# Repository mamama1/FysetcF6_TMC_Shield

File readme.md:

This shield has been inspired from the great SilentStepStick Protector boards by Watterott.
Source, see https://github.com/watterott/SilentStepStick

Some silkscreen has been stripped but besides that, Watterott's design has been used completely unchanged regarding the protection diode circuitry.

This board allows you to apply up to 42V (max. recommended) or up to 50V (absolute maximum, not recommended) to your motors by not connecting the VM pin to the F6 mainboard.

This repository has been released under the Creative Commons Attribution Share-Alike License: https://creativecommons.org/licenses/by-sa/4.0/

The original repository owned by Watterott, containing the SilentStepStick and Protector source files was released under the same license, see here: https://github.com/watterott/SilentStepStick/blob/master/README.md

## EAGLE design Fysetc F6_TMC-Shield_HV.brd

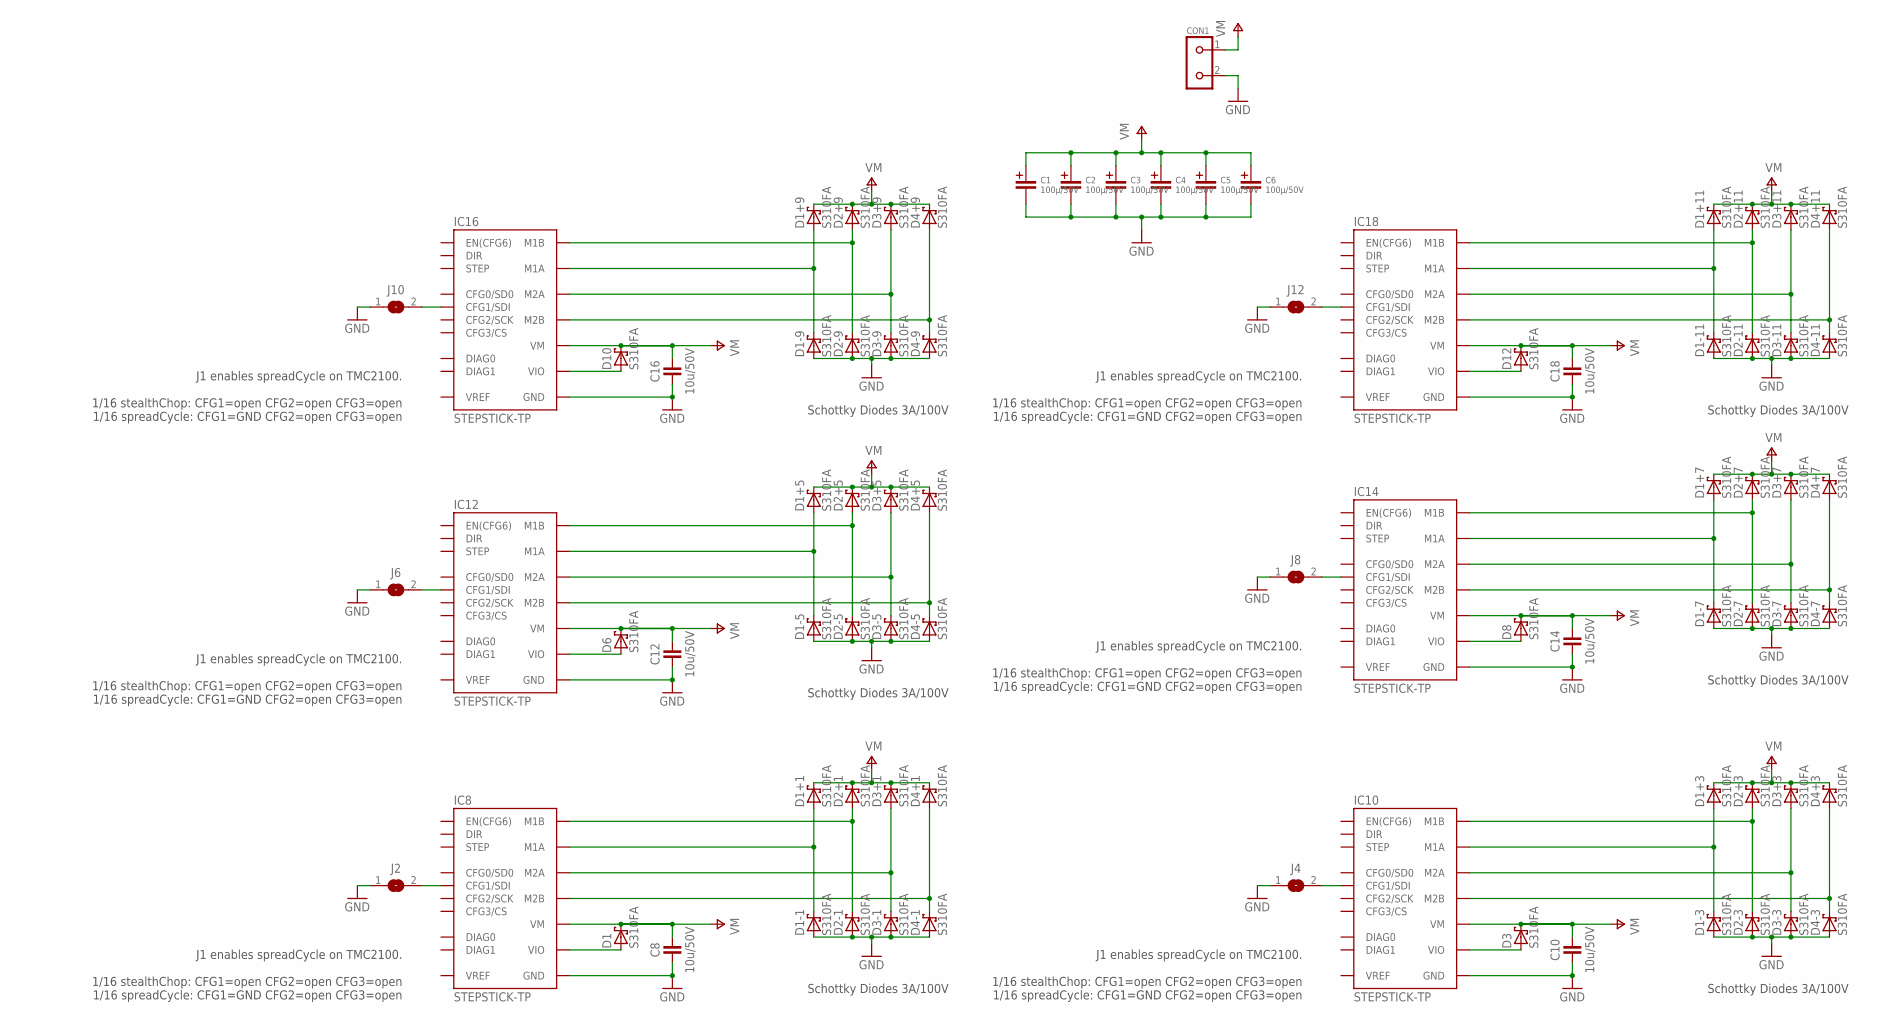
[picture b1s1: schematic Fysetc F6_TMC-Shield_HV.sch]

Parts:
C1, C2, C3, C4, C5, C6: 100µ/50V; C+/3.5/8
C8, C10, C12, C14, C16, C18: 10u/50V; C1210
CON1: KL2691311500002; KL2-691311500002
D1, D1+1, D1+3, D1+5, D1+7, D1+9, D1+11, D1-1, D1-3, D1-5, D1-7, D1-9, D1-11, D2+1, D2+3, D2+5, D2+7, D2+9, D2+11, D2-1, D2-3, D2-5, D2-7, D2-9, D2-11, D3, D3+1, D3+3, D3+5, D3+7, D3+9, D3+11, D3-1, D3-3, D3-5, D3-7, D3-9, D3-11, D4+1, D4+3, D4+5, D4+7, D4+9, D4+11, D4-1, D4-3, D4-5, D4-7, D4-9, D4-11, D6, D8, D10, D12: S310FA; SOD123
IC8, IC10, IC12, IC14, IC16, IC18: STEPSTICK-TP; STEPSTICK_TP
J2, J4, J6, J8, J10, J12: JUMPER2-0603-NC; JUMPER2-0603_NC

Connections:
GND: C1.-, C2.-, C3.-, C4.-, C5.-, C6.-, C8.1, C10.1, C12.1, C14.1, C16.1, C18.1, CON1.2, D1-1.A, D1-3.A, D1-5.A, D1-7.A, D1-9.A, D1-11.A, D2-1.A, D2-3.A, D2-5.A, D2-7.A, D2-9.A, D2-11.A, D3-1.A, D3-3.A, D3-5.A, D3-7.A, D3-9.A, D3-11.A, D4-1.A, D4-3.A, D4-5.A, D4-7.A, D4-9.A, D4-11.A, IC8.GND@1 (GND), IC8.GND@2 (GND), IC10.GND@1 (GND), IC10.GND@2 (GND), IC12.GND@1 (GND), IC12.GND@2 (GND), IC14.GND@1 (GND), IC14.GND@2 (GND), IC16.GND@1 (GND), IC16.GND@2 (GND), IC18.GND@1 (GND), IC18.GND@2 (GND), J2.1, J4.1, J6.1, J8.1, J10.1, J12.1
M1A1: D1+1.A, D1-1.C, IC8.M1A
M1A3: D1+3.A, D1-3.C, IC10.M1A
M1A5: D1+5.A, D1-5.C, IC12.M1A
M1A7: D1+7.A, D1-7.C, IC14.M1A
M1A9: D1+9.A, D1-9.C, IC16.M1A
M1A11: D1+11.A, D1-11.C, IC18.M1A
M1B1: D2+1.A, D2-1.C, IC8.M1B
M1B3: D2+3.A, D2-3.C, IC10.M1B
M1B5: D2+5.A, D2-5.C, IC12.M1B
M1B7: D2+7.A, D2-7.C, IC14.M1B
M1B9: D2+9.A, D2-9.C, IC16.M1B
M1B11: D2+11.A, D2-11.C, IC18.M1B
M2A1: D3+1.A, D3-1.C, IC8.M2A
M2A3: D3+3.A, D3-3.C, IC10.M2A
M2A5: D3+5.A, D3-5.C, IC12.M2A
M2A7: D3+7.A, D3-7.C, IC14.M2A
M2A9: D3+9.A, D3-9.C, IC16.M2A
M2A11: D3+11.A, D3-11.C, IC18.M2A
M2B1: D4+1.A, D4-1.C, IC8.M2B
M2B3: D4+3.A, D4-3.C, IC10.M2B
M2B5: D4+5.A, D4-5.C, IC12.M2B
M2B7: D4+7.A, D4-7.C, IC14.M2B
M2B9: D4+9.A, D4-9.C, IC16.M2B
M2B11: D4+11.A, D4-11.C, IC18.M2B
unnamed: IC8.CFG1 (CFG1/SDI), J2.2
unnamed: IC10.CFG1 (CFG1/SDI), J4.2
unnamed: IC12.CFG1 (CFG1/SDI), J6.2
unnamed: IC14.CFG1 (CFG1/SDI), J8.2
unnamed: IC16.CFG1 (CFG1/SDI), J10.2
unnamed: IC18.CFG1 (CFG1/SDI), J12.2
VIO1: D1.A, IC8.VIO
VIO3: D3.A, IC10.VIO
VIO5: D6.A, IC12.VIO
VIO7: D8.A, IC14.VIO
VIO9: D10.A, IC16.VIO
VIO11: D12.A, IC18.VIO
VM: C1.+, C2.+, C3.+, C4.+, C5.+, C6.+, C8.2, C10.2, C12.2, C14.2, C16.2, C18.2, CON1.1, D1.C, D1+1.C, D1+3.C, D1+5.C, D1+7.C, D1+9.C, D1+11.C, D2+1.C, D2+3.C, D2+5.C, D2+7.C, D2+9.C, D2+11.C, D3.C, D3+1.C, D3+3.C, D3+5.C, D3+7.C, D3+9.C, D3+11.C, D4+1.C, D4+3.C, D4+5.C, D4+7.C, D4+9.C, D4+11.C, D6.C, D8.C, D10.C, D12.C, IC8.VM, IC10.VM, IC12.VM, IC14.VM, IC16.VM, IC18.VM

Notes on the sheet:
Schottky Diodes 3A/100V
J1 enables spreadCycle on TMC2100. 1/16 stealthChop: CFG1=open CFG2=open CFG3=open 1/16 spreadCycle: CFG1=GND CFG2=open CFG3=open

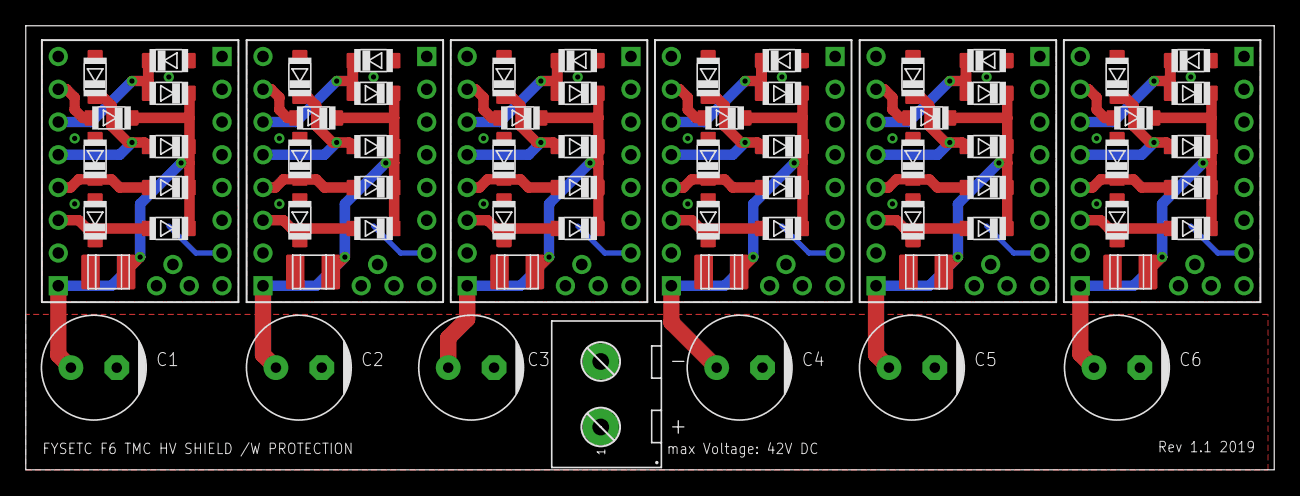
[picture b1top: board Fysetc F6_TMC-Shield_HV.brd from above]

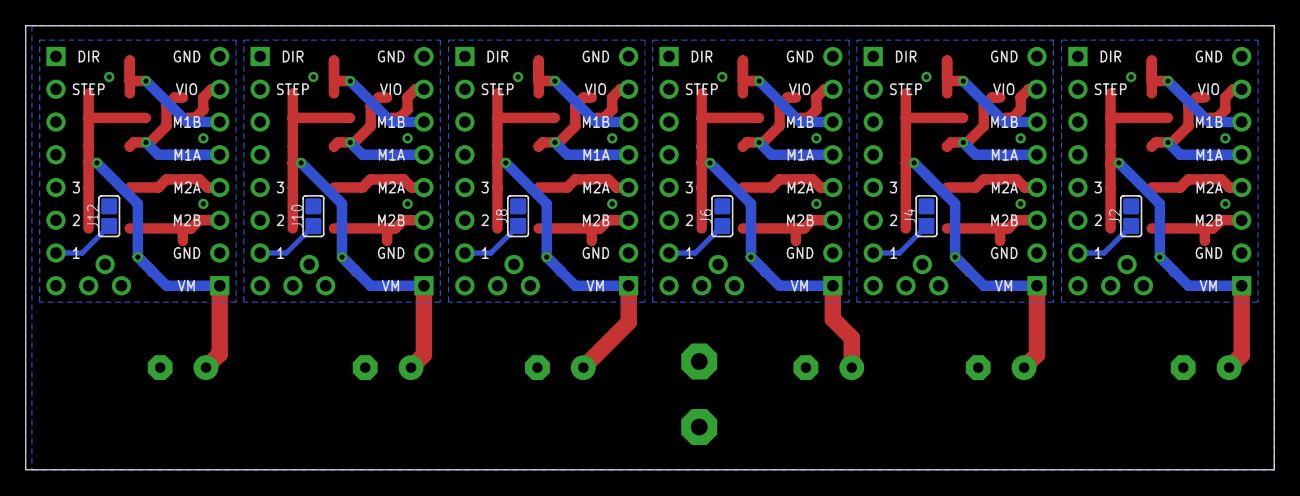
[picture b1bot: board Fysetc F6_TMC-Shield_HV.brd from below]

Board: 2 copper layers, 96.8 x 34.4 mm, 79 parts (6 on the bottom side), 38 nets.

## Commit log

2019-04-13 add preview and schematic
